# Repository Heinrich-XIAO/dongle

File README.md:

# htkbd
Theo's perfect keyboard

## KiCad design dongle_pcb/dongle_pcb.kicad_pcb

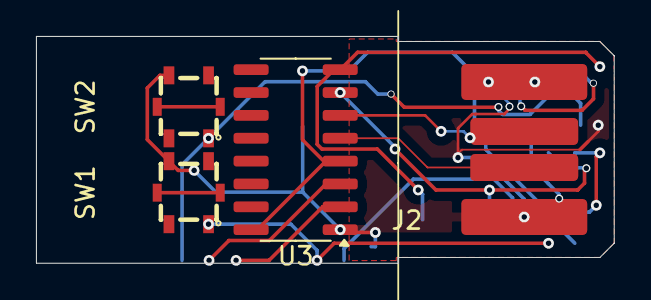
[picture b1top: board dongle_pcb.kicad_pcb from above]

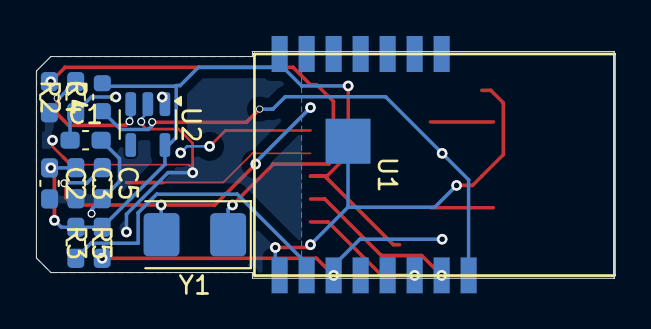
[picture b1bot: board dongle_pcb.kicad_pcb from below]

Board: 2 copper layers, 32.1 x 12.6 mm, 16 parts (12 on the bottom side), 13 nets.

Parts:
C1, C2: 1uF; C_0603_1608Metric_Pad1.08x0.95mm_HandSolder
C3: 100nF; C_0603_1608Metric_Pad1.08x0.95mm_HandSolder
C4, C5: 30pF; C_0603_1608Metric_Pad1.08x0.95mm_HandSolder
J2: USB_A_PCB_Edge_receptacle
R2: 1k; C_0603_1608Metric_Pad1.08x0.95mm_HandSolder
R3, R5: 10k; C_0603_1608Metric_Pad1.08x0.95mm_HandSolder
R4: 10k; C_0603_1608Metric
SW1, SW2: TS-1077S-01726; KEY-SMD_4P-L3.1-W3.1-P2.00_TS-1077S-01726
U1: ESP-M2
U2: AP2112K-3.3; SOT-23-5
U3: CH340G; SOIC-16_3.9x9.9mm_P1.27mm
Y1: 12MHz; Crystal_SMD_5032-2Pin_5.0x3.2mm

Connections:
+3.3V: C2.1, C3.1, R3.2, R4.2, R5.1, U1.7 (VCC), U2.5 (VOUT), U3.4 (V3), U3.16 (VCC)
D+: J2.3 (D+), U3.5 (UD+)
D-: J2.2 (D-), U3.6 (UD-)
GND: C1.2, C2.2, C3.2, C4.2, C5.2, J2.4 (GND), SW1.3, SW2.3, U1.8 (GND), U1.16 (GND), U2.2 (GND), U3.1 (GND)
unnamed: R3.1, SW1.1, U1.10 (GPIO0)
unnamed: R5.2, U1.9 (GPIO2)
unnamed: R4.1, SW2.1, U1.15 (RST)
unnamed: U1.13 (RX), U3.2 (TXD)
unnamed: U1.14 (TX), U3.3 (RXD)
unnamed: R2.2, U2.3 (EN)
unnamed: C5.1, U3.7 (XI), Y1.2
unnamed: C4.1, U3.8 (XO), Y1.1
VBUS: C1.1, J2.1 (VBUS), R2.1, U2.1 (VIN)

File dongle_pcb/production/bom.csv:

Designator,Footprint,Quantity,Value,LCSC Part #
"C1, C2",0603,2,1uF,
C3,0603,1,100nF,
"C4, C5",0603,2,30pF,
J2,USB_A_PCB_Edge_receptacle,1,USB_A_PCB_Edge_receptacle,
R2,0603,1,1k,
"R3, R4, R5",0603,3,10k,
"SW1, SW2",KEY-SMD_4P-L3.1-W3.1-P2.00_TS-1077S-01726,2,TS-1077S-01726,C455260
U1,ESP-M2,1,ESP-M2,
U2,SOT-23-5,1,AP2112K-3.3,
U3,SOIC-16_3.9x9.9mm_P1.27mm,1,CH340G,
Y1,Crystal_SMD_5032-2Pin_5.0x3.2mm,1,12MHz,

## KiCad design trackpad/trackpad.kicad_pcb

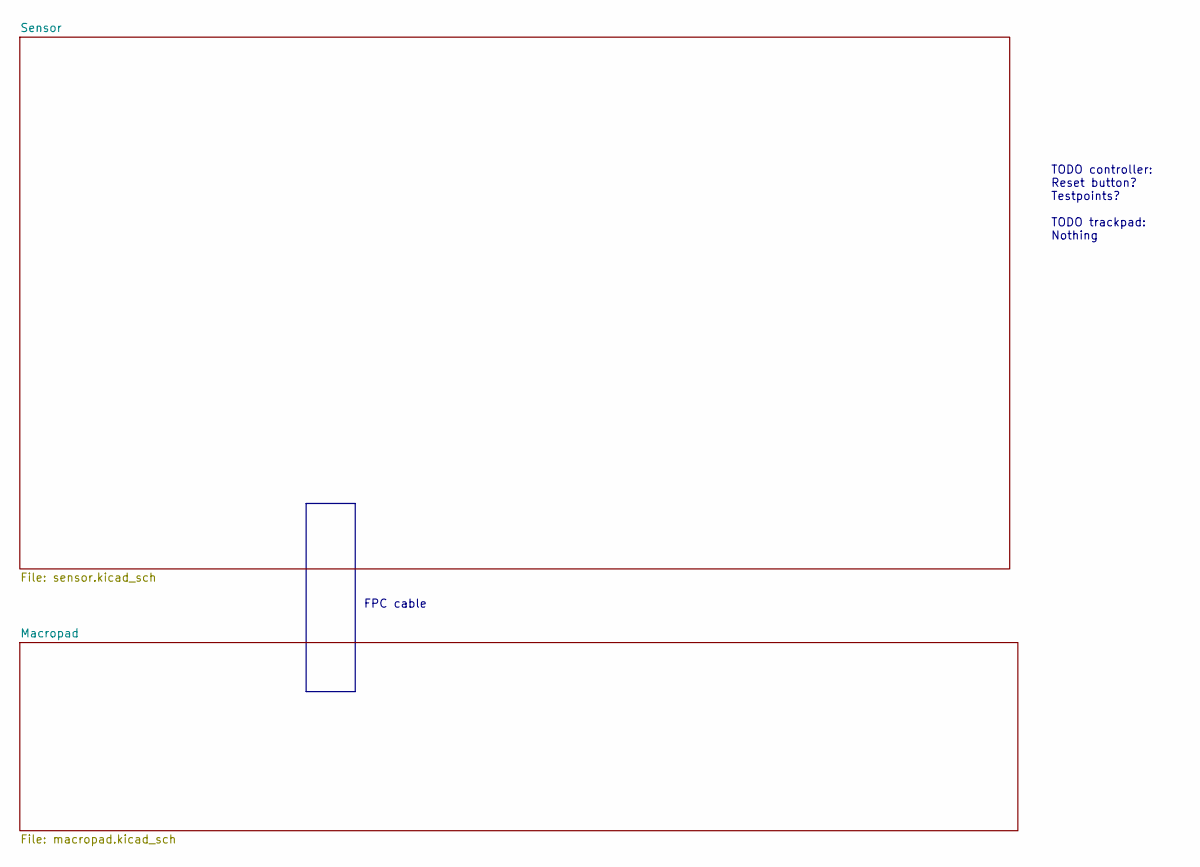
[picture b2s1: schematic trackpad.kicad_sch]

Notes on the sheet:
TODO controller: Reset button? Testpoints? TODO trackpad: Nothing
FPC cable

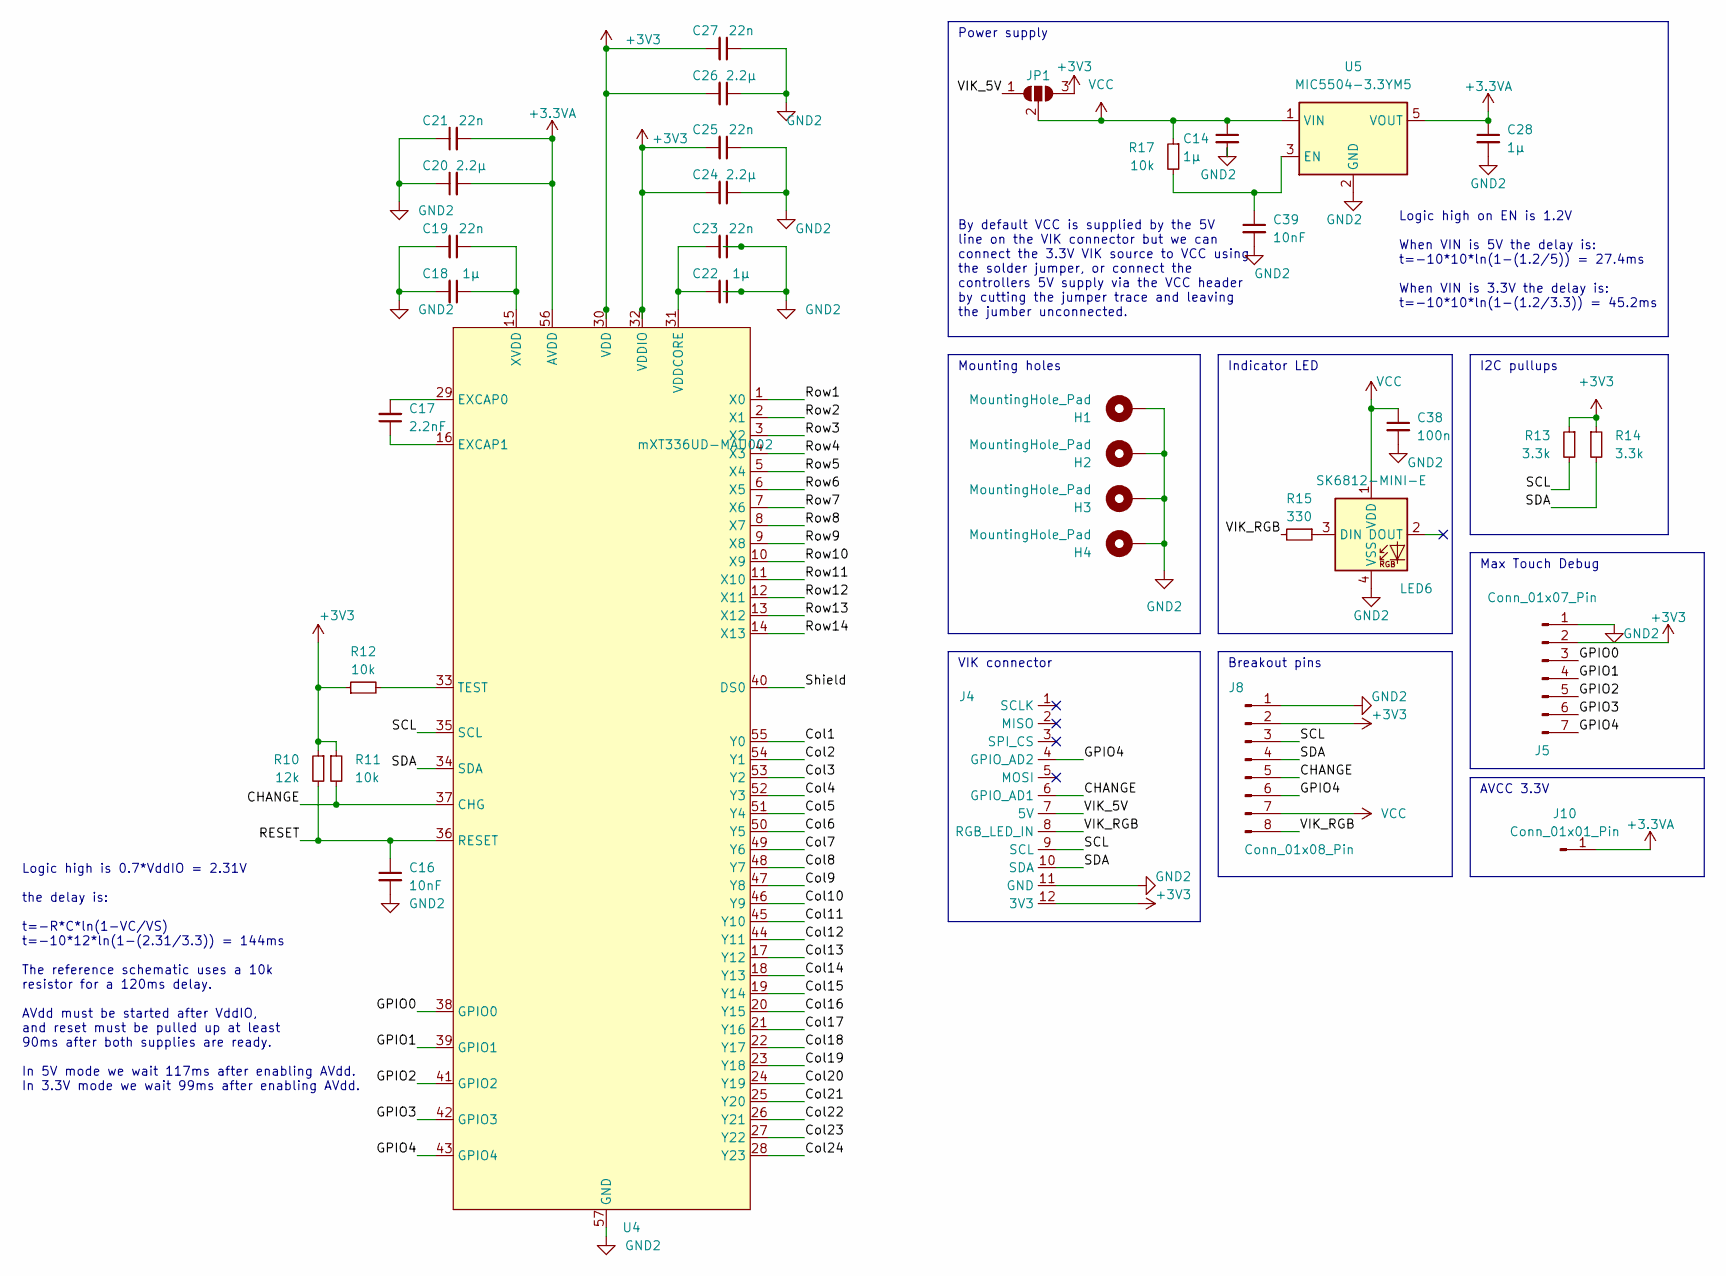
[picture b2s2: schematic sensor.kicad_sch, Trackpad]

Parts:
C14, C18, C22, C28: 1µ; C_0402_1005Metric; LCSC C52923
C16, C39: 10nF; C_0402_1005Metric; LCSC C15195
C17: 2.2nF; C_0603_1608Metric; LCSC C1604
C19, C21, C23, C25, C27: 22n; C_0402_1005Metric; LCSC C1532
C20, C24, C26: 2.2µ; C_0402_1005Metric; LCSC C12530
C38: 100n; C_0402_1005Metric; LCSC C1525
H1, H2, H3, H4: MountingHole_Pad; MountingHole_3.2mm_M3_Pad_Via
J4: vik-module-connector-vertical; LCSC C262499
J5: Conn_01x07_Pin; PinHeader_1x07_P1.27mm_Vertical
J8: Conn_01x08_Pin; PinHeader_1x08_P2.54mm_Vertical
J10: Conn_01x01_Pin; PinHeader_1x01_P1.27mm_Vertical
JP1: SolderJumper_3_Open; SolderJumper-3_P1.3mm_Bridged2Bar12_RoundedPad1.0x1.5mm
LED6: SK6812-MINI-E; LED_6028R; LCSC C5149201
R10: 12k; R_0402_1005Metric; LCSC C25752
R11, R12, R17: 10k; R_0402_1005Metric; LCSC C25744
R13, R14: 3.3k; R_0402_1005Metric
R15: 330; R_0402_1005Metric; LCSC C25104
U4: mXT336UD-MAU002; QFN-56_EP_6x6_Pitch0.35mm
U5: MIC5504-3.3YM5; SOT-23-5; Mouser Part Number 998-MIC5323-3.3YD5TR

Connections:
+3.3VA: C20.2, C21.2, C28.1, J10.1, U4.56 (AVDD), U5.5 (VOUT)
+3V3: C24.2, C25.2, C26.2, C27.2, J4.12 (3V3), J5.2, J8.2, JP1.3 (B), R10.1, R11.1, R12.1, R13.1, R14.1, U4.30 (VDD), U4.32 (VDDIO)
/Sensor/CHANGE: J4.6 (GPIO_AD1), J8.5, R11.2, U4.37 (CHG)
/Sensor/Col1: U4.55 (Y0)
/Sensor/Col2: U4.54 (Y1)
/Sensor/Col3: U4.53 (Y2)
/Sensor/Col4: U4.52 (Y3)
/Sensor/Col5: U4.51 (Y4)
/Sensor/Col6: U4.50 (Y5)
/Sensor/Col7: U4.49 (Y6)
/Sensor/Col8: U4.48 (Y7)
/Sensor/Col9: U4.47 (Y8)
/Sensor/Col10: U4.46 (Y9)
/Sensor/Col11: U4.45 (Y10)
/Sensor/Col12: U4.44 (Y11)
/Sensor/Col13: U4.17 (Y12)
/Sensor/Col14: U4.18 (Y13)
/Sensor/Col15: U4.19 (Y14)
/Sensor/Col16: U4.20 (Y15)
/Sensor/Col17: U4.21 (Y16)
/Sensor/Col18: U4.22 (Y17)
/Sensor/Col19: U4.23 (Y18)
/Sensor/Col20: U4.24 (Y19)
/Sensor/Col21: U4.25 (Y20)
/Sensor/Col22: U4.26 (Y21)
/Sensor/Col23: U4.27 (Y22)
/Sensor/Col24: U4.28 (Y23)
/Sensor/GPIO0: J5.3, U4.38 (GPIO0)
/Sensor/GPIO1: J5.4, U4.39 (GPIO1)
/Sensor/GPIO2: J5.5, U4.41 (GPIO2)
/Sensor/GPIO3: J5.6, U4.42 (GPIO3)
/Sensor/GPIO4: J4.4 (GPIO_AD2), J5.7, J8.6, U4.43 (GPIO4)
/Sensor/RESET: C16.1, R10.2, U4.36 (RESET)
/Sensor/Row1: U4.1 (X0)
/Sensor/Row2: U4.2 (X1)
/Sensor/Row3: U4.3 (X2)
/Sensor/Row4: U4.4 (X3)
/Sensor/Row5: U4.5 (X4)
/Sensor/Row6: U4.6 (X5)
/Sensor/Row7: U4.7 (X6)
/Sensor/Row8: U4.8 (X7)
/Sensor/Row9: U4.9 (X8)
/Sensor/Row10: U4.10 (X9)
/Sensor/Row11: U4.11 (X10)
/Sensor/Row12: U4.12 (X11)
/Sensor/Row13: U4.13 (X12)
/Sensor/Row14: U4.14 (X13)
/Sensor/SCL: J4.9 (SCL), J8.3, R13.2, U4.35 (SCL)
/Sensor/SDA: J4.10 (SDA), J8.4, R14.2, U4.34 (SDA)
/Sensor/Shield: U4.40 (DS0)
/Sensor/VIK_5V: J4.7 (5V), JP1.1 (A)
/Sensor/VIK_RGB: J4.8 (RGB_LED_IN), J8.8, R15.2
GND2: C14.2, C16.2, C18.2, C19.2, C20.1, C21.1, C22.1, C23.1, C24.1, C25.1, C26.1, C27.1, C28.2, C38.2, C39.2, H1.1, H2.1, H3.1, H4.1, J4.11 (GND), J5.1, J8.1, LED6.4 (VSS), U4.57 (GND), U5.2 (GND)
unnamed: LED6.3 (DIN), R15.1
unnamed: C17.2, U4.29 (EXCAP0)
unnamed: C17.1, U4.16 (EXCAP1)
unnamed: R12.2, U4.33 (TEST)
unnamed: C22.2, C23.2, U4.31 (VDDCORE)
unnamed: C18.1, C19.1, U4.15 (XVDD)
unnamed: C39.1, R17.2, U5.3 (EN)
VCC: C14.1, C38.1, J8.7, JP1.2 (C), LED6.1 (VDD), R17.1, U5.1 (VIN)

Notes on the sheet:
Indicator LED
Mounting holes
By default VCC is supplied by the 5V line on the VIK connector but we can connect the 3.3V VIK source to VCC using the solder jumper, or connect the controllers 5V supply via the VCC header by cutting the jumper trace and leaving the jumber unconnected.
Logic high is 0.7*VddIO = 2.31V the delay is: t=-R*C*ln(1-VC/VS) t=-10*12*ln(1-(2.31/3.3)) = 144ms The reference schematic uses a 10k resistor for a 120ms delay. AVdd must be started after VddIO, and reset must be pulled up at least 90ms after both supplies are ready. In 5V mode we wait 117ms after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
I2C pullups
Power supply
Logic high on EN is 1.2V When VIN is 5V the delay is: t=-10*10*ln(1-(1.2/5)) = 27.4ms When VIN is 3.3V the delay is: t=-10*10*ln(1-(1.2/3.3)) = 45.2ms
VIK connector
Breakout pins
AVCC 3.3V
Max Touch Debug

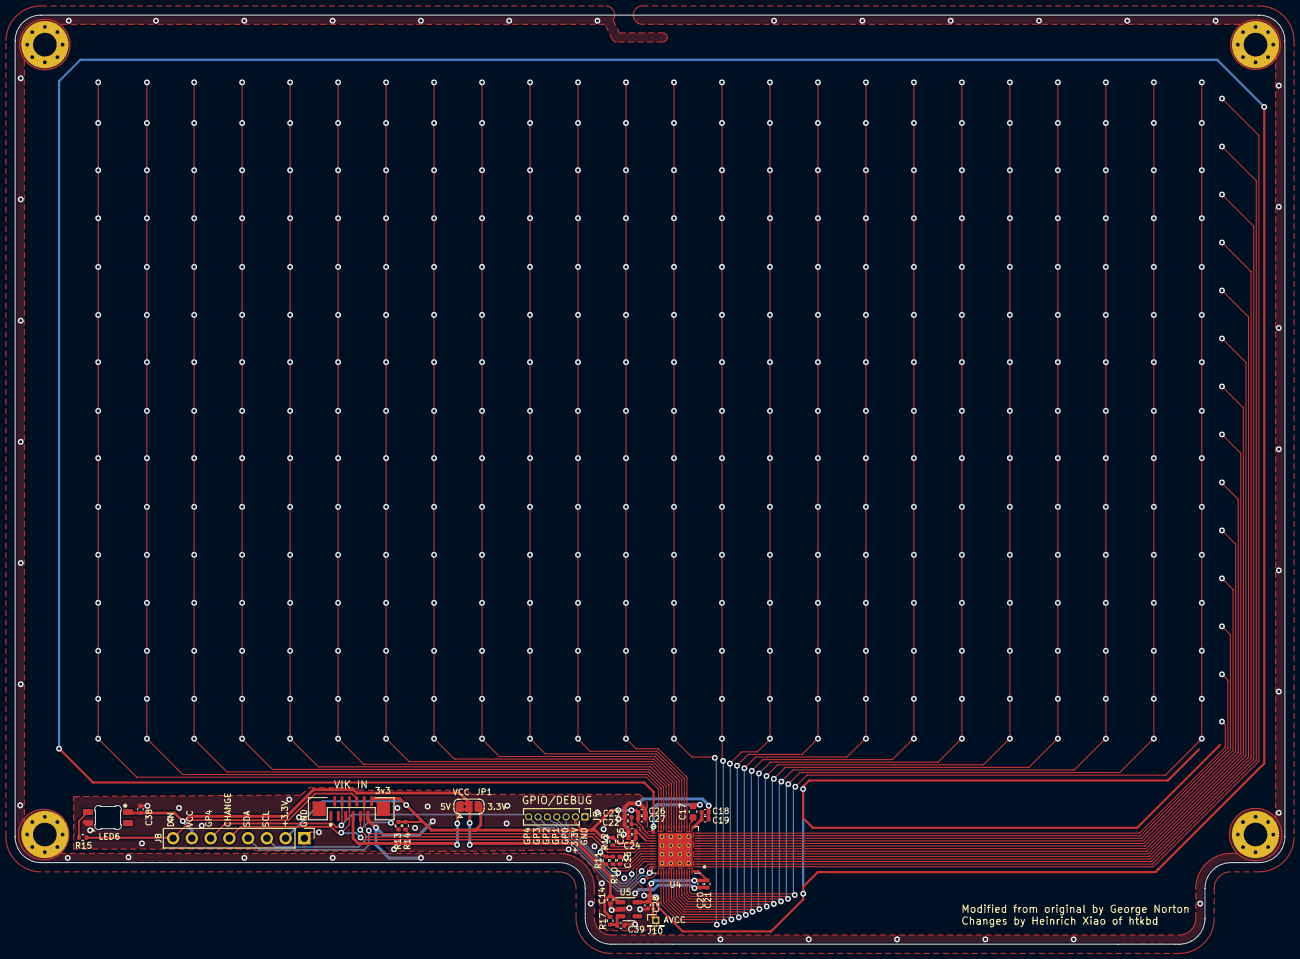
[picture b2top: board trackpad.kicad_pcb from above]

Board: 2 copper layers, 172.0 x 125.9 mm, 35 parts (0 on the bottom side), 22 nets.

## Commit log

2025-07-05 schematic prob done
2025-07-07 journal for yesterday and schematic done except for battery and stuff
2025-07-08 i think thats all i did
2025-07-21 stuff
2025-07-23 restart dongle and finally make ~~america~~ pcbs great again
2025-07-28 pcb layed out
